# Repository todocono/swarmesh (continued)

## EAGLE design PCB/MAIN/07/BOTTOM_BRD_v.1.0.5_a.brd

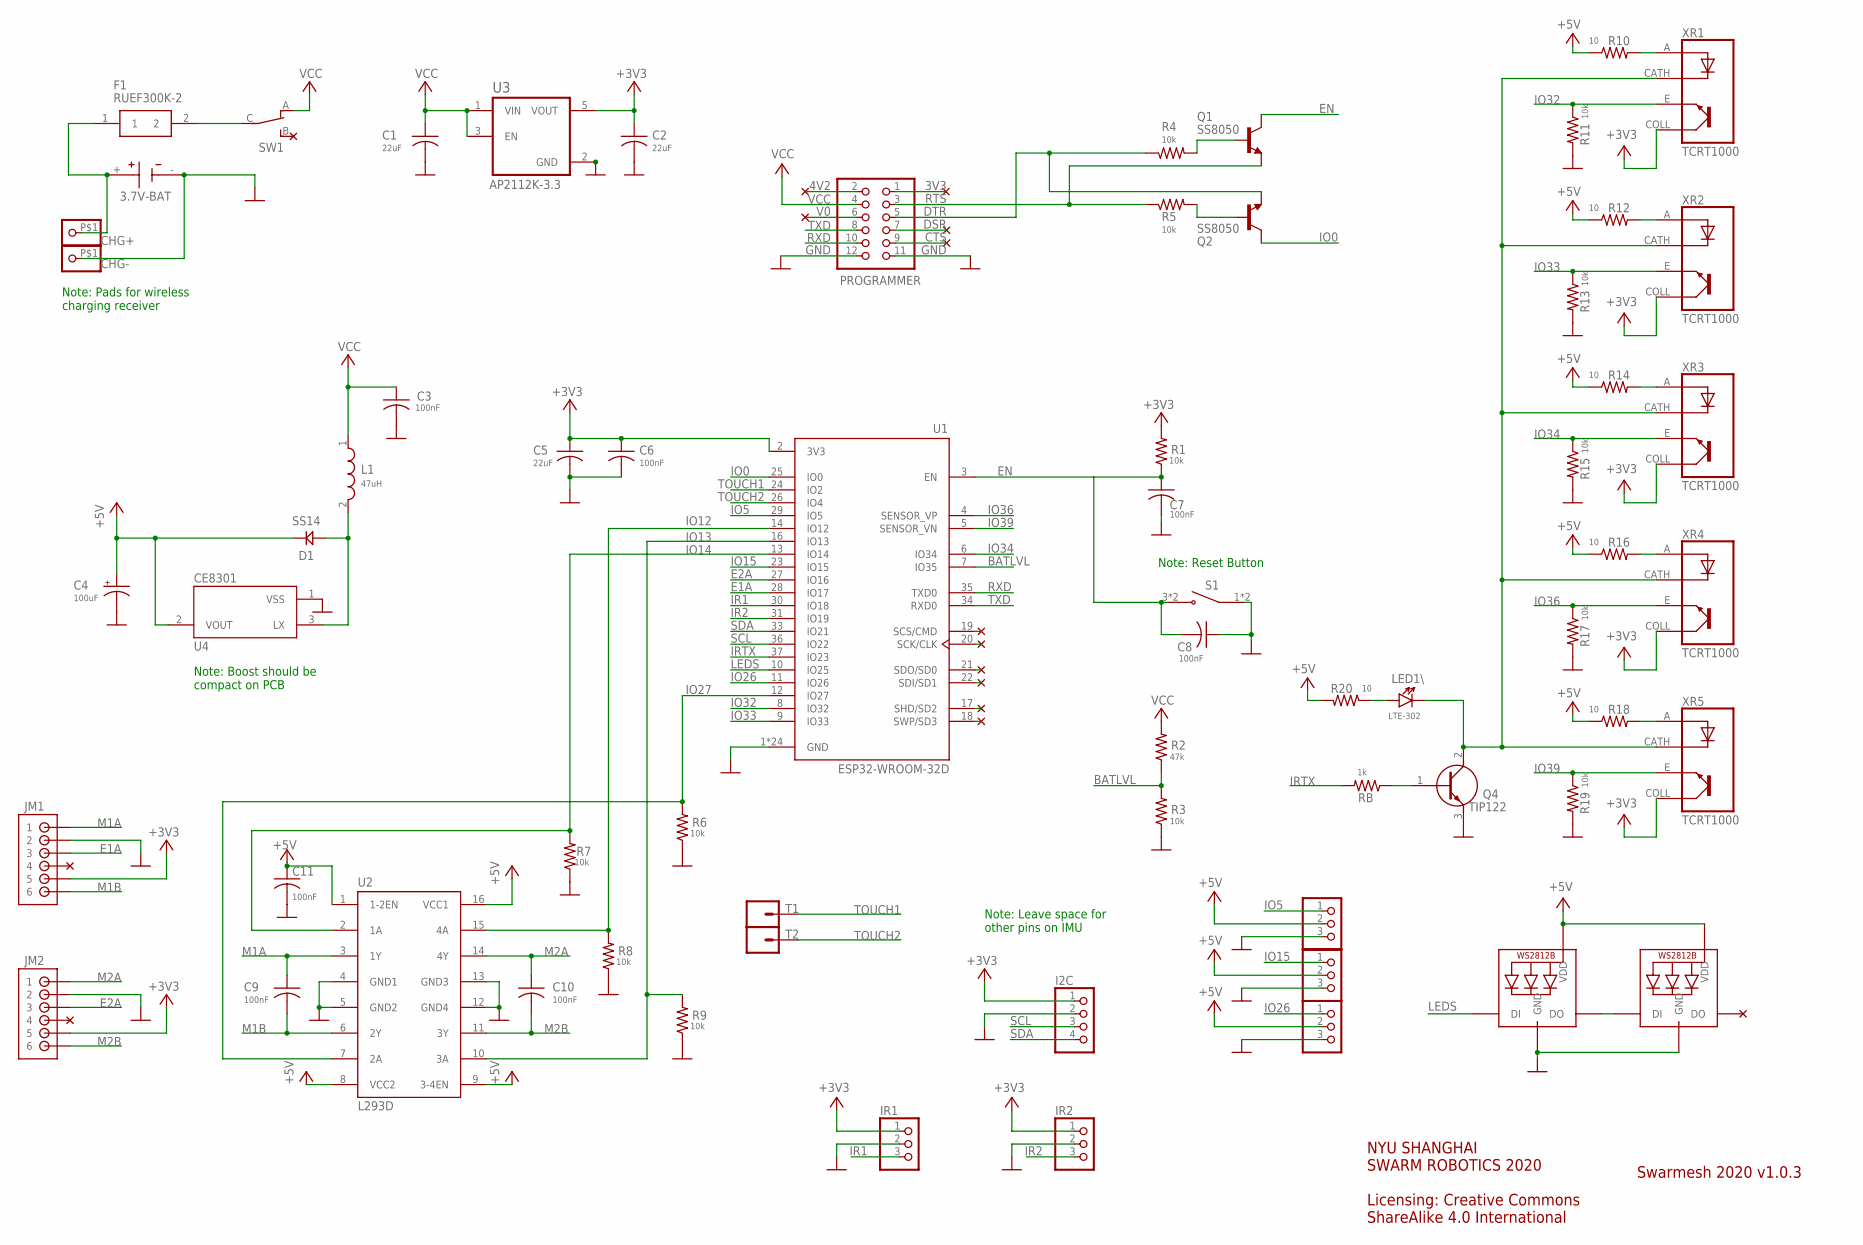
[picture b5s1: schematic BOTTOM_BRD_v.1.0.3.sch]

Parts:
BT: 3.7V-BAT; BAT_6S-AA
C1, C2, C5: 22uF; C0805
C3, C6, C7, C8, C9, C10, C11: 100nF; C0805
C4: 100uF; 153CLV-0605
CHARGING: WS2812B5050; WS2812B
CHG+: PINHD-1X1-BIGPOGO; 1X1-BIGPOGO
CHG-: PINHD-1X1-BIGPOGO; 1X1-BIGPOGO
D1: SS14; DO214
F1: RUEF300K-2; RUEF300K2
GPIO5, GPIO15, GPIO26: PINHD-1X3; 1X03
I2C: PINHD-1X4; 1X04
IR1, IR2: PINHD-1X3; 1X03
JM1, JM2: B6B-ZR
L1: 47uH; INDP5858X480N
LED1\: LTE-302
PROGRAMMER: PINHD-2X6; 2X06
Q1, Q2: SS8050; SOT23
Q4: TIP122; TO270P460X1020X2008-3P
R1, R3, R4, R5, R6, R7, R8, R9, R11, R13, R15, R17, R19: 10k; M0805
R2: 47k; M0805
R10, R12, R14, R16, R18, R20: 10; M0805
RB: 1k; M0805
S1: 2-1437565-9; SW_2-1437565-9
STATE: WS2812B5050; WS2812B
SW1: CS12ANW03
T1, T2: CONN_01SPRING-CONN; SPRING-CONNECTOR
U1: ESP32-WROOM-32D; MODULE_ESP32-WROOM-32D
U2: L293D; DIL16
U3: AP2112K-3.3; SOT95P285X140-5N
U4: CE8301; REG_MCP1702T-3302E/MB
XR1, XR2, XR3, XR4, XR5: TCRT1000; XDCR_TCRT1000

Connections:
3V3: PROGRAMMER.1
4V2: PROGRAMMER.2
+3V3: C2.1, C5.1, C6.1, I2C.1, IR1.1, IR2.1, JM1.5, JM2.5, R1.2, U1.2 (3V3), U3.5 (VOUT), XR1.COLL (CO), XR2.COLL (CO), XR3.COLL (CO), XR4.COLL (CO), XR5.COLL (CO)
+5V: C4.+, C11.1, CHARGING.1-VDD (VDD), D1.CATHODE (KATHODE), GPIO5.2, GPIO15.2, GPIO26.2, R10.1, R12.1, R14.1, R16.1, R18.1, R20.2, STATE.1-VDD (VDD), U2.1 (1-2EN), U2.8 (VCC2), U2.9 (3-4EN), U2.16 (VCC1), U4.2 (VOUT)
BATLVL: R2.1, R3.2, U1.7 (IO35)
CTS: PROGRAMMER.9
DSR: PROGRAMMER.7
DTR: PROGRAMMER.5, Q2.2 (E), R4.1
E1A: JM1.3, U1.28 (IO17)
E2A: JM2.3, U1.27 (IO16)
EN: C7.1, C8.2, Q1.3 (C), R1.1, S1.3 (NO), S1.4 (NO), U1.3 (EN)
GND: BT.-, C1.2, C2.2, C3.2, C4.-, C5.2, C6.2, C7.2, C8.1, C11.2, CHARGING.3-GND (GND), CHG-.P$1, GPIO5.3, GPIO15.3, GPIO26.3, I2C.2, IR1.2, IR2.2, JM1.2, JM2.2, PROGRAMMER.11, PROGRAMMER.12, Q4.3 (E), R3.1, R6.1, R7.1, R8.1, R9.1, R11.2, R13.2, R15.2, R17.2, R19.2, S1.1 (COM), S1.2 (COM), STATE.3-GND (GND), U1.1 (GND), U1.15 (GND), U1.38 (GND), U1.39_1 (GND), U1.39_2 (GND), U1.39_3 (GND), U1.39_4 (GND), U1.39_5 (GND), U1.39_6 (GND), U1.39_7 (GND), U1.39_8 (GND), U1.39_9 (GND), U1.39_10 (GND), U1.39_11 (GND), U1.39_12 (GND), U1.39_13 (GND), U1.39_14 (GND), U1.39_15 (GND), U1.39_16 (GND), U1.39_17 (GND), U1.39_18 (GND), U1.39_19 (GND), U1.39_20 (GND), U1.39_21 (GND), U2.4 (GND1), U2.5 (GND2), U2.12 (GND4), U2.13 (GND3), U3.2 (GND), U4.1 (VSS)
IO0: Q2.3 (C), U1.25 (IO0)
IO5: GPIO5.1, U1.29 (IO5)
IO12: R8.2, U1.14 (IO12), U2.15 (4A)
IO13: R9.2, U1.16 (IO13), U2.10 (3A)
IO14: R7.2, U1.13 (IO14), U2.2 (1A)
IO15: GPIO15.1, U1.23 (IO15)
IO26: GPIO26.1, U1.11 (IO26)
IO27: R6.2, U1.12 (IO27), U2.7 (2A)
IO32: R11.1, U1.8 (IO32), XR1.E
IO33: R13.1, U1.9 (IO33), XR2.E
IO34: R15.1, U1.6 (IO34), XR3.E
IO36: R17.1, U1.4 (SENSOR_VP), XR4.E
IO39: R19.1, U1.5 (SENSOR_VN), XR5.E
IR1: IR1.3, U1.30 (IO18)
IR2: IR2.3, U1.31 (IO19)
IRTX: RB.2, U1.37 (IO23)
LEDS: CHARGING.4-DIN (DI), U1.10 (IO25)
M1A: C9.1, JM1.1, U2.3 (1Y)
M1B: C9.2, JM1.6, U2.6 (2Y)
M2A: C10.1, JM2.1, U2.14 (4Y)
M2B: C10.2, JM2.6, U2.11 (3Y)
unnamed: BT.+, CHG+.P$1, F1.1
unnamed: Q4.1 (B), RB.1
unnamed: F1.2, SW1.C
unnamed: D1.ANODE, L1.2, U4.3 (LX)
unnamed: R12.2, XR2.A
unnamed: R16.2, XR4.A
unnamed: LED1\.C, Q4.2 (C), XR1.CATH (C), XR2.CATH (C), XR3.CATH (C), XR4.CATH (C), XR5.CATH (C)
unnamed: CHARGING.2-DOUT (DO), STATE.4-DIN (DI)
unnamed: R14.2, XR3.A
unnamed: R18.2, XR5.A
unnamed: Q1.1 (B), R4.2
unnamed: R10.2, XR1.A
unnamed: LED1\.A, R20.1
unnamed: Q2.1 (B), R5.2
RTS: PROGRAMMER.3, Q1.2 (E), R5.1
RXD: PROGRAMMER.10, U1.35 (TXD0)
SCL: I2C.3, U1.36 (IO22)
SDA: I2C.4, U1.33 (IO21)
TOUCH1: T1.P$2, U1.24 (IO2)
TOUCH2: T2.P$2, U1.26 (IO4)
TXD: PROGRAMMER.8, U1.34 (RXD0)
V0: PROGRAMMER.6
VCC: C1.1, C3.1, L1.1, PROGRAMMER.4, R2.2, SW1.A, U3.1 (VIN), U3.3 (EN)

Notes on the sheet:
Note: Pads for wireless charging receiver
Note: Boost should be compact on PCB
Note: Leave space for other pins on IMU
Note: Reset Button
Swarmesh 2020 v1.0.3
NYU SHANGHAI SWARM ROBOTICS 2020 Licensing: Creative Commons ShareAlike 4.0 International

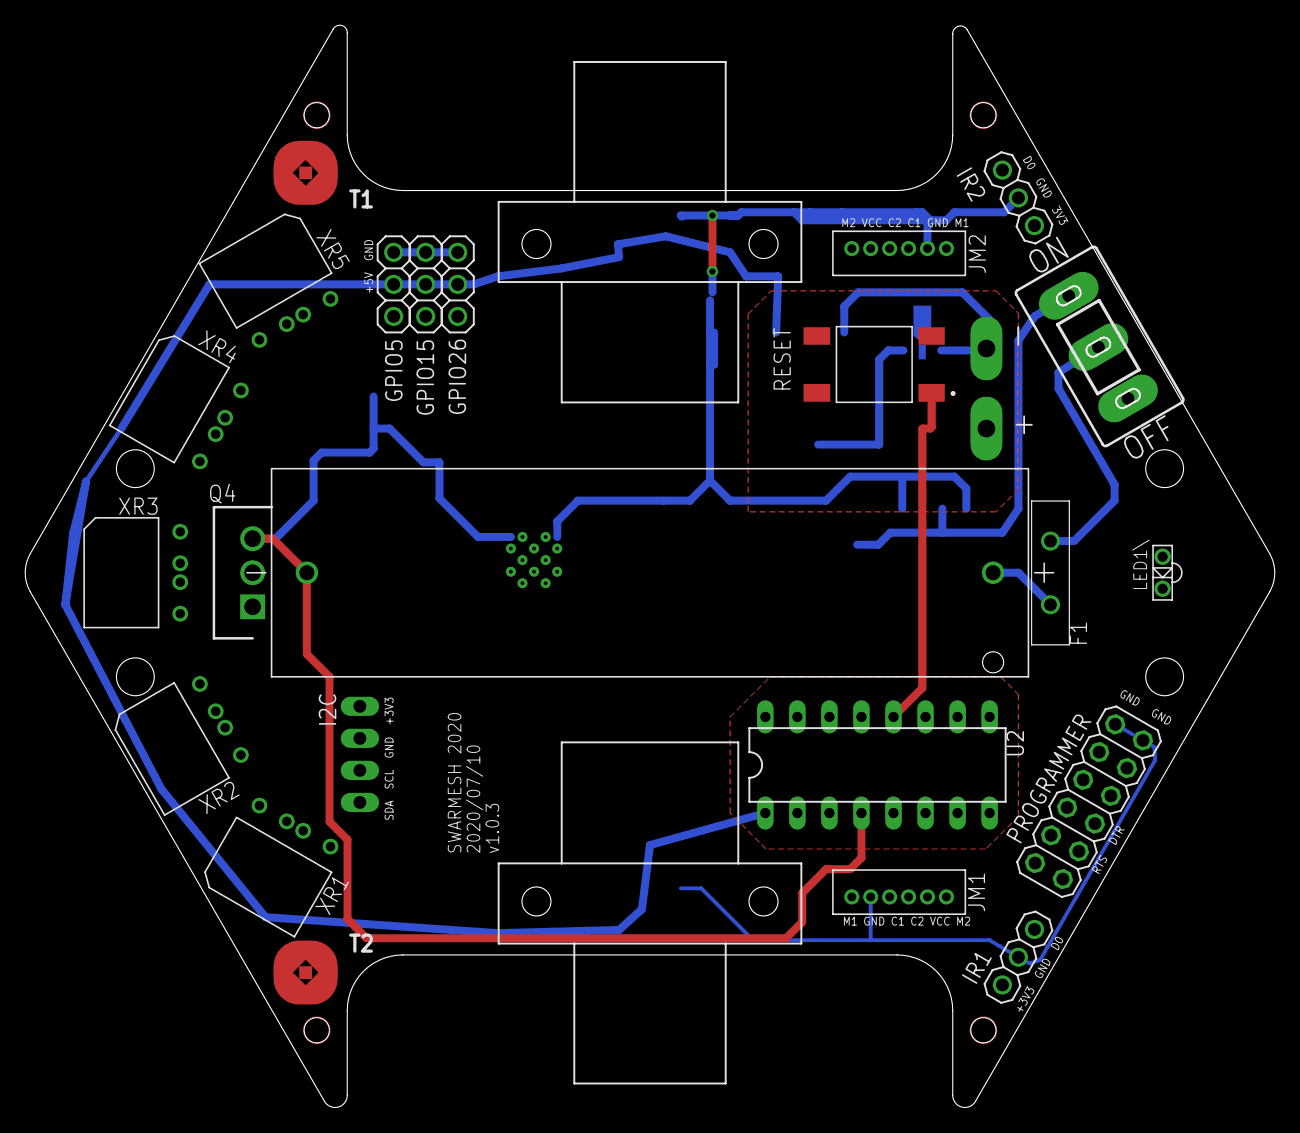
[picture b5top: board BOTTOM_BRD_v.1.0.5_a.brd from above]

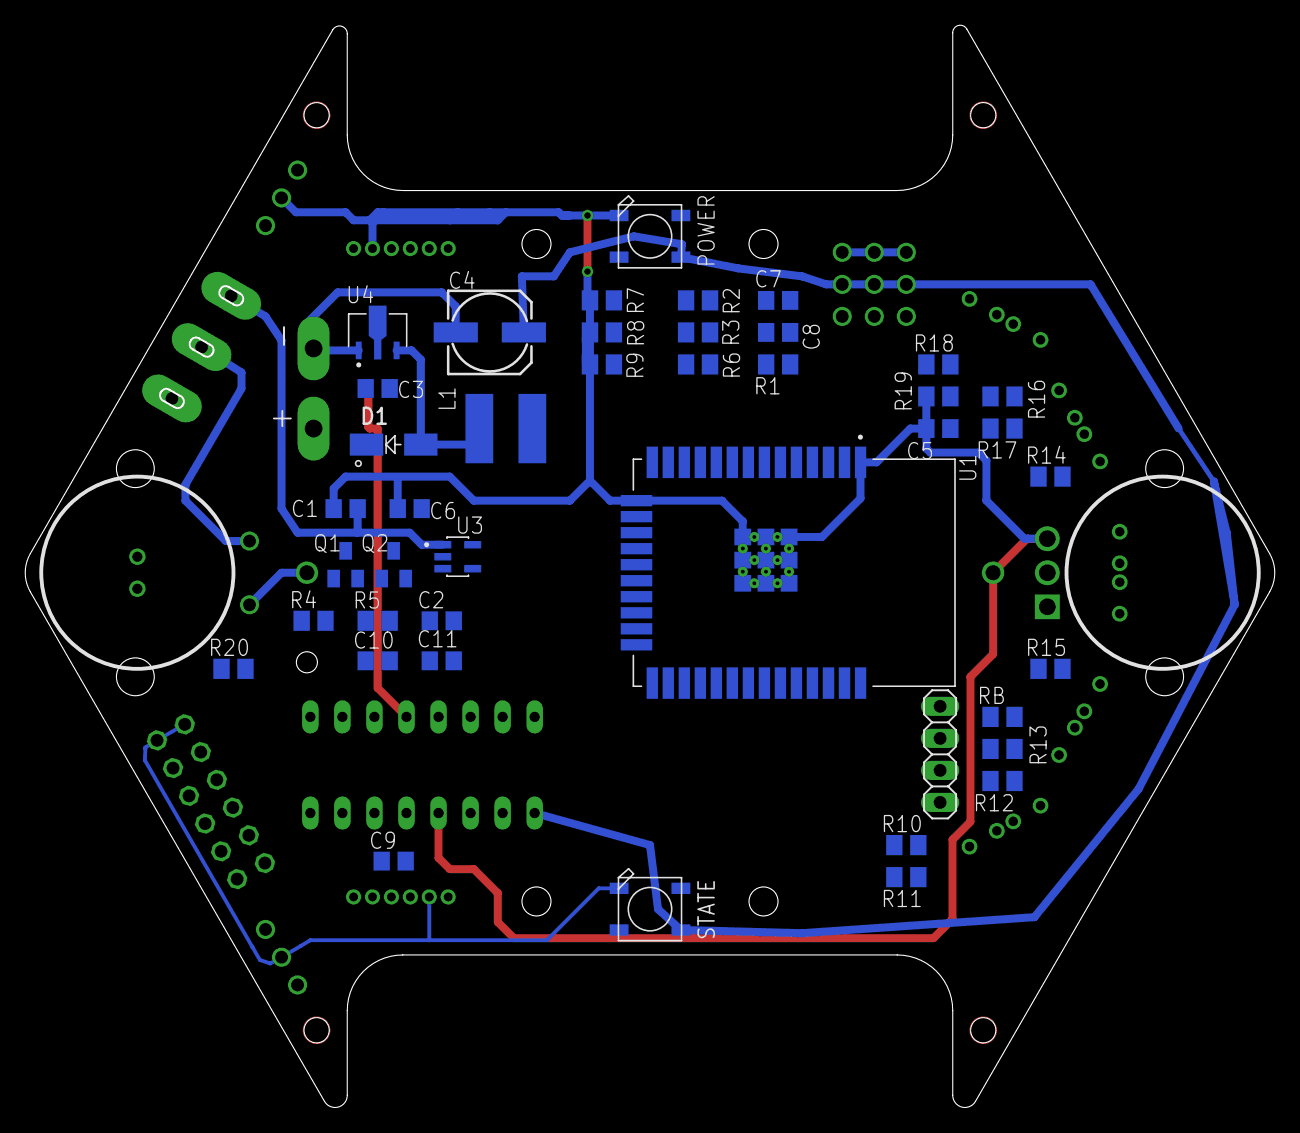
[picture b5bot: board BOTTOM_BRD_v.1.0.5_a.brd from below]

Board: 2 copper layers, 99.1 x 85.8 mm, 66 parts (43 on the bottom side), 51 nets.
